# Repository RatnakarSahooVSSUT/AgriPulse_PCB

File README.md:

<div align="center">

# AgriPulse PCB

**Custom Embedded Hardware Design using KiCad**

A custom two-layer PCB designed for the AgriPulse Smart Agriculture Monitoring System, integrating ESP32-based control, agricultural sensor interfaces, RS485 communication and power management.

<br><br>

<br><br>

</div>

---

## Project Overview

AgriPulse is a Smart Agriculture Monitoring System developed to integrate multiple agricultural and environmental sensors into a centralized IoT-based monitoring platform.

This repository contains the custom hardware design developed for the AgriPulse system. The PCB is built around the ESP32 DevKit V1 and provides dedicated interfaces for sensor acquisition, communication, power management and peripheral connectivity.

The design incorporates interfaces for soil moisture monitoring, temperature and humidity sensing, external temperature probes and RS485-based NPK sensor communication.

The objective is to provide a modular and centralized hardware platform for agricultural data acquisition and IoT integration.

---

## PCB Design Gallery

<div align="center">

### 3D PCB Visualization

<br>

### PCB Layout

<br>

### Circuit Schematic

</div>

---

## Hardware Specifications

| Parameter | Specification |
|:---|:---|
| Main Controller | ESP32 DevKit V1 |
| RS485 Transceiver | MAX3485ECSA_T |
| Voltage Regulator | TLV75533PDBV |
| Input Supply | 12V DC |
| Regulated Supply | 3.3V |
| Communication | UART / RS485 |
| Sensor Interfaces | Soil Moisture, DHT22, Temperature Probe |
| PCB Architecture | 2-Layer |
| PCB Design Software | KiCad |
| Component Technology | SMD and Through-Hole |

---

## Power Management

The PCB incorporates a dedicated power input and regulation stage.

- 12V DC barrel jack input.
- Polyfuse-based input protection.
- TVS diode-based transient protection.
- PMOS-based power protection.
- TLV75533PDBV 3.3V voltage regulation.
- Input and output decoupling capacitors.
- Dedicated power and ground distribution.

---

## Sensor & Communication Interfaces

### Sensor Interfacing

- Soil moisture sensor interface.
- DHT22 temperature and humidity interface.
- External temperature probe interface.
- Additional GPIO-based peripheral connections.

### RS485 Communication

The board integrates a MAX3485ECSA_T transceiver for differential communication with external agricultural sensors, including the NPK sensor.

- RS485 A/B differential interface.
- UART communication with ESP32.
- Driver and receiver enable control.
- Dedicated external communication connector.

### User Interface

- Start/Stop push-button interface.
- Screen control button.
- Wi-Fi status indication.
- Alert status indication.
- Start/Stop status indication.

---

## Design Highlights

- ESP32 DevKit V1 integration.
- MAX3485-based RS485 communication.
- Dedicated NPK sensor connectivity.
- Multiple agricultural sensor interfaces.
- 12V DC power input.
- Integrated power protection and 3.3V regulation.
- Dedicated peripheral connectors.
- User control and status indication interfaces.
- Two-layer PCB architecture.
- Custom KiCad symbols, footprints and 3D models.
- Copper routing and GND plane design.
- Dedicated PCB mounting holes.

---

## Major Components

| Component | Function |
|:---|:---|
| ESP32 DevKit V1 | Main controller |
| MAX3485ECSA_T | RS485 transceiver |
| TLV75533PDBV | 3.3V voltage regulator |
| PMOS | Power protection |
| Polyfuse | Input current protection |
| TVS Diode | Transient voltage protection |
| Zener Diode | Voltage protection |
| LEDs | Status indication |
| Capacitors | Filtering and decoupling |
| Resistors | Biasing and current limiting |

---

## PCB Design Tools

<div align="center">

</div>

- **KiCad:** Schematic capture and PCB layout.
- **ESP32:** Embedded controller platform.
- **MAX3485:** RS485 differential communication.
- **Custom Libraries:** Component symbols, footprints and 3D models.

---

## Repository Contents

| File / Folder | Description |
|:---|:---|
| `AgriPulse_pcb.kicad_pro` | Main KiCad project file |
| `AgriPulse_pcb.kicad_pcb` | PCB layout document |
| `AgriPulse_pcb.kicad_sch` | Circuit schematic |
| `Libraries/agripulse.pretty/` | Custom PCB footprints |
| `Libraries/DEVKIT_V1_ESP32-WROOM-32/` | ESP32 symbol, footprint and 3D model |
| `Libraries/MAX3485ECSA_T/` | MAX3485 symbol, footprint and 3D model |
| `images/` | PCB renders, layout and schematic images |
| `.gitignore` | Git version control exclusions |

---

## Getting Started

Clone the repository:

```bash
git clone https://github.com/RatnakarSahooVSSUT/AgriPulse_PCB.git
```

Open `AgriPulse_pcb.kicad_pro` using KiCad.

Configure the custom symbol, footprint and 3D model libraries if required.

The repository includes the schematic, PCB layout and custom component libraries used in the design.

---

## Applications

- Smart agriculture monitoring.
- Soil moisture monitoring.
- Environmental parameter acquisition.
- Temperature and humidity monitoring.
- NPK sensor integration.
- RS485-based agricultural sensor communication.
- IoT-based agricultural data acquisition.

---

## Author

<div align="center">

### Ratnakar Sahoo

**Electronics & Telecommunication Engineering**

Veer Surendra Sai University of Technology (VSSUT), Odisha

Interested in Embedded Systems, PCB Design, Hardware Development, FPGA and IoT Technologies.

<br><br>

</div>

---

<div align="center">

**AGRIPULSE | SMART AGRICULTURE | EMBEDDED SYSTEMS**

Designed with KiCad.

</div>

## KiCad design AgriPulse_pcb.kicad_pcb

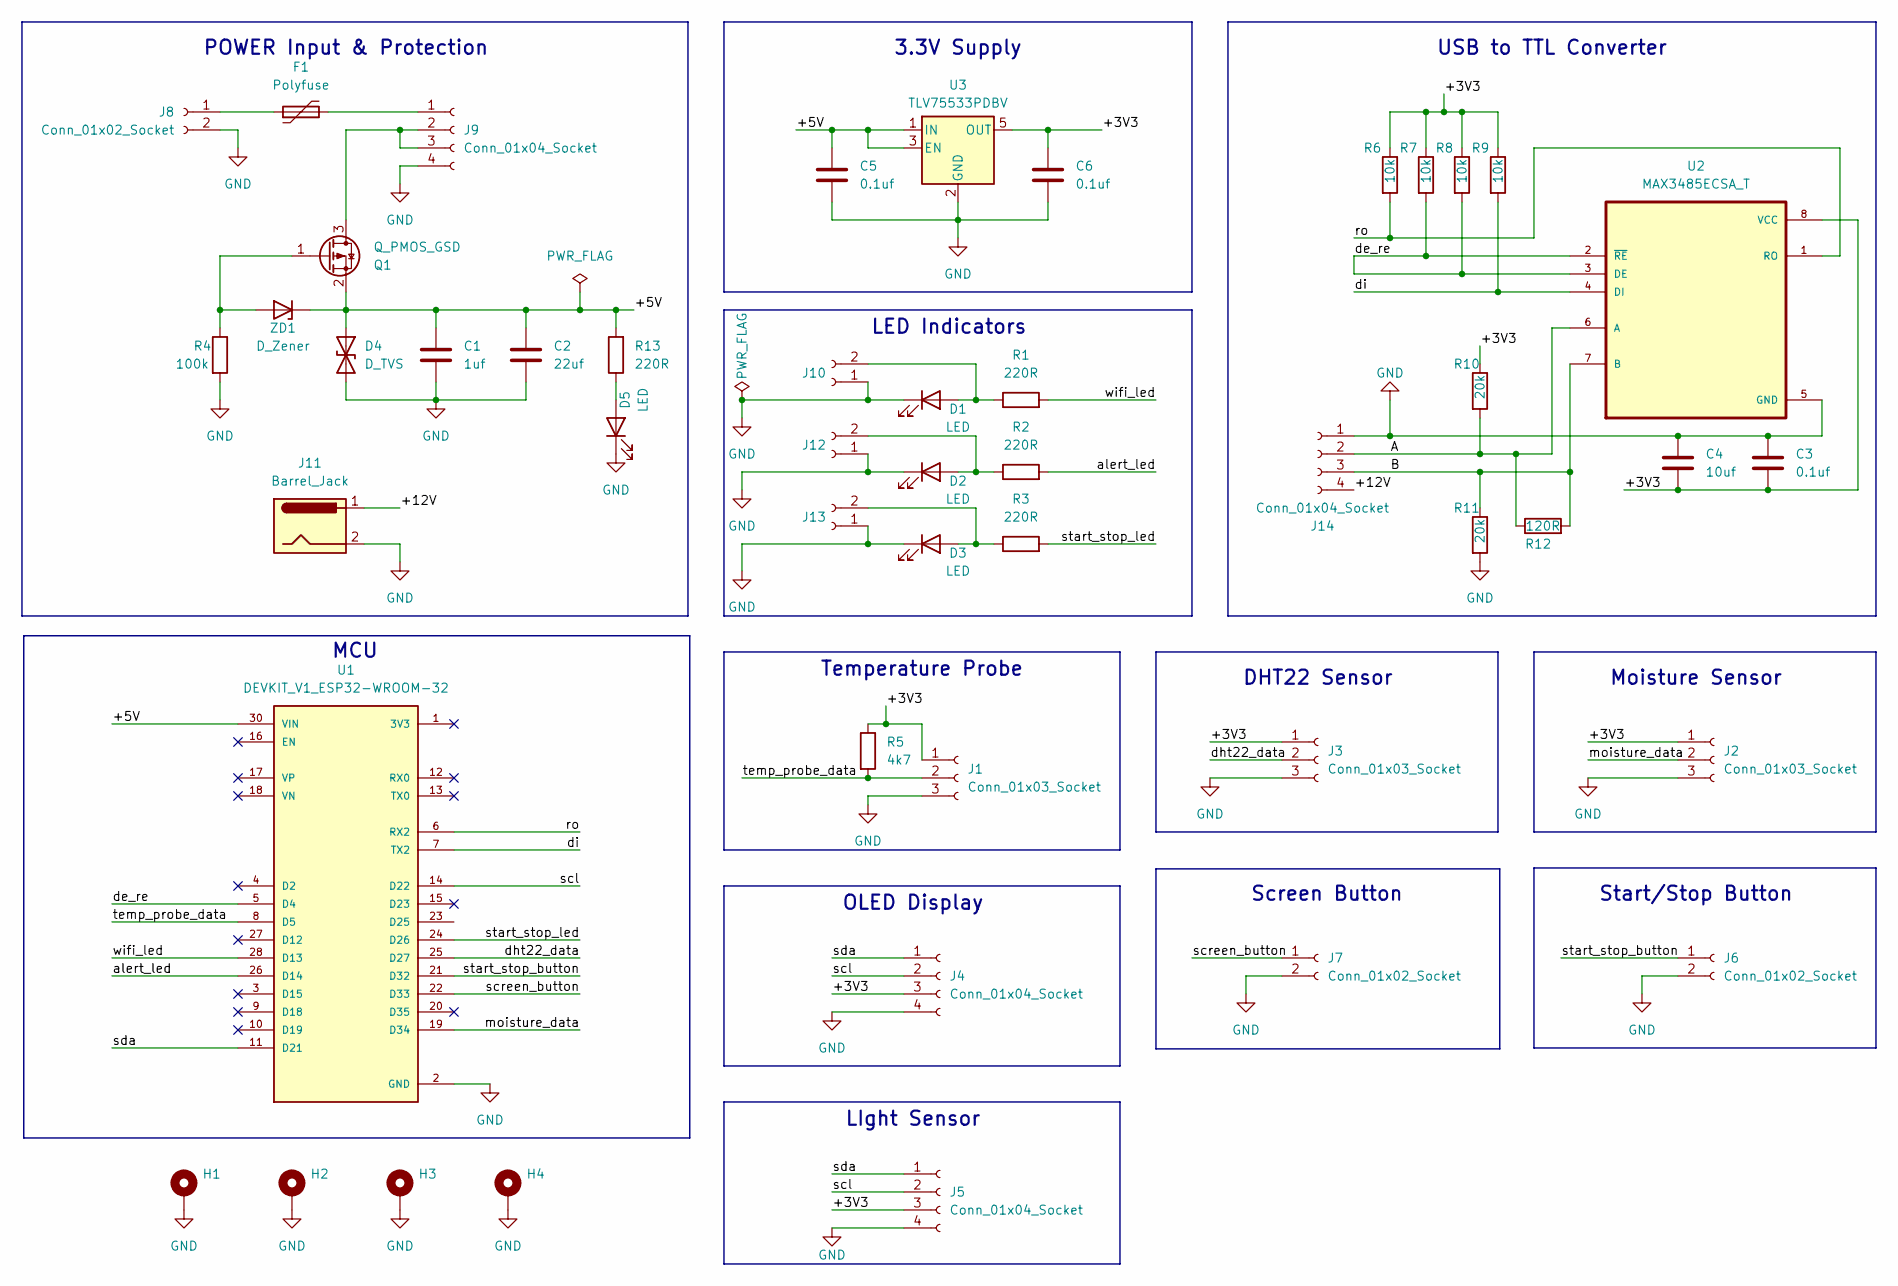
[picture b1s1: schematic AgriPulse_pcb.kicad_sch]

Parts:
C1: 1uf; C_1206_3216Metric_Pad1.33x1.80mm_HandSolder
C2: 22uf; C_1206_3216Metric_Pad1.33x1.80mm_HandSolder
C3, C5, C6: 0.1uf; C_1206_3216Metric_Pad1.33x1.80mm_HandSolder
C4: 10uf; C_1206_3216Metric_Pad1.33x1.80mm_HandSolder
D1, D2, D3, D5: LED; LED_D3.0mm
D4: D_TVS; D_SMB
F1: Polyfuse; Fuse_1812_4532Metric
H1, H2, H3, H4: MountingHole_Pad; MountingHole_2.2mm_M2_Pad_Via
J1, J2, J3: Conn_01x03_Socket; JST_XH_B3B-XH-A_1x03_P2.50mm_Vertical
J4, J5, J9, J14: Conn_01x04_Socket; JST_XH_B4B-XH-A_1x04_P2.50mm_Vertical
J6, J7, J8, J10, J12, J13: Conn_01x02_Socket; JST_XH_B2B-XH-A_1x02_P2.50mm_Vertical
J11: Barrel_Jack; BarrelJack_Horizontal
Q1: Q_PMOS_GSD; SOT-23
R1, R2, R3, R13: 220R; R_1206_3216Metric_Pad1.30x1.75mm_HandSolder
R4: 100k; R_1206_3216Metric_Pad1.30x1.75mm_HandSolder
R5: 4k7; R_1206_3216Metric_Pad1.30x1.75mm_HandSolder
R6, R7, R8, R9: 10k; R_1206_3216Metric_Pad1.30x1.75mm_HandSolder
R10, R11: 20k; R_1206_3216Metric_Pad1.30x1.75mm_HandSolder
R12: 120R; R_1206_3216Metric_Pad1.30x1.75mm_HandSolder
U1: DEVKIT_V1_ESP32-WROOM-32; MODULE_DEVKIT_V1_ESP32-WROOM-32; MPN DEVKIT V1 ESP32-WROOM-32
U2: MAX3485ECSA_T; SOIC127P600X175-8N; MPN MAX3485ECSA+T
U3: TLV75533PDBV; SOT-23-5_HandSoldering
ZD1: D_Zener; D_SOD-323

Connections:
/+3V3: C3.2, C4.2, C6.1, J1.1, J2.1, J3.1, J4.3, J5.3, R5.1, R6.1, R7.1, R8.1, R9.1, R10.1, U2.8 (VCC), U3.5 (OUT)
/+5V: C1.1, C2.1, C5.1, D4.1 (A1), Q1.2 (S), R13.2, U1.30 (VIN), U3.1 (IN), U3.3 (EN), ZD1.1 (K)
/+12V: J11.1, J14.4
/A: J14.2, R10.2, R12.1, U2.6 (A)
/B: J14.3, R11.1, R12.2, U2.7 (B)
/alert_led: R2.2, U1.26 (D14)
/de_re: R7.2, R8.2, U1.5 (D4), U2.2 (~RE), U2.3 (DE)
/dht22_data: J3.2, U1.25 (D27)
/di: R9.2, U1.7 (TX2), U2.4 (DI)
/moisture_data: J2.2, U1.19 (D34)
/ro: R6.2, U1.6 (RX2), U2.1 (RO)
/scl: J4.2, J5.2, U1.14 (D22)
/screen_button: J7.1, U1.22 (D33)
/sda: J4.1, J5.1, U1.11 (D21)
/start_stop_button: J6.1, U1.21 (D32)
/start_stop_led: R3.2, U1.24 (D26)
/temp_probe_data: J1.2, R5.2, U1.8 (D5)
/wifi_led: R1.2, U1.28 (D13)
GND: C1.2, C2.2, C3.1, C4.1, C5.2, C6.2, D1.1 (K), D2.1 (K), D3.1 (K), D4.2 (A2), D5.1 (K), H1.1 (1_1), H2.1 (1_1), H3.1 (1_1), H4.1 (1_1), J1.3, J2.3, J3.3, J4.4, J5.4, J6.2, J7.2, J8.2, J9.4, J10.1, J11.2, J12.1, J13.1, J14.1, R4.2, R11.2, U1.2 (GND), U1.29 (GND), U2.5 (GND), U3.2 (GND)
unnamed: D1.2 (A), J10.2, R1.1
unnamed: D2.2 (A), J12.2, R2.1
unnamed: D3.2 (A), J13.2, R3.1
unnamed: D5.2 (A), R13.1
unnamed: F1.1, J8.1
unnamed: F1.2, J9.1
unnamed: J9.2, J9.3, Q1.3 (D)
unnamed: Q1.1 (G), R4.1, ZD1.2 (A)

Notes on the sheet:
Start/Stop Button
USB to TTL Converter
LIght Sensor
Temperature Probe
Screen Button
POWER Input & Protection
LED Indicators
OLED Display
MCU
3.3V Supply
Moisture Sensor
DHT22 Sensor

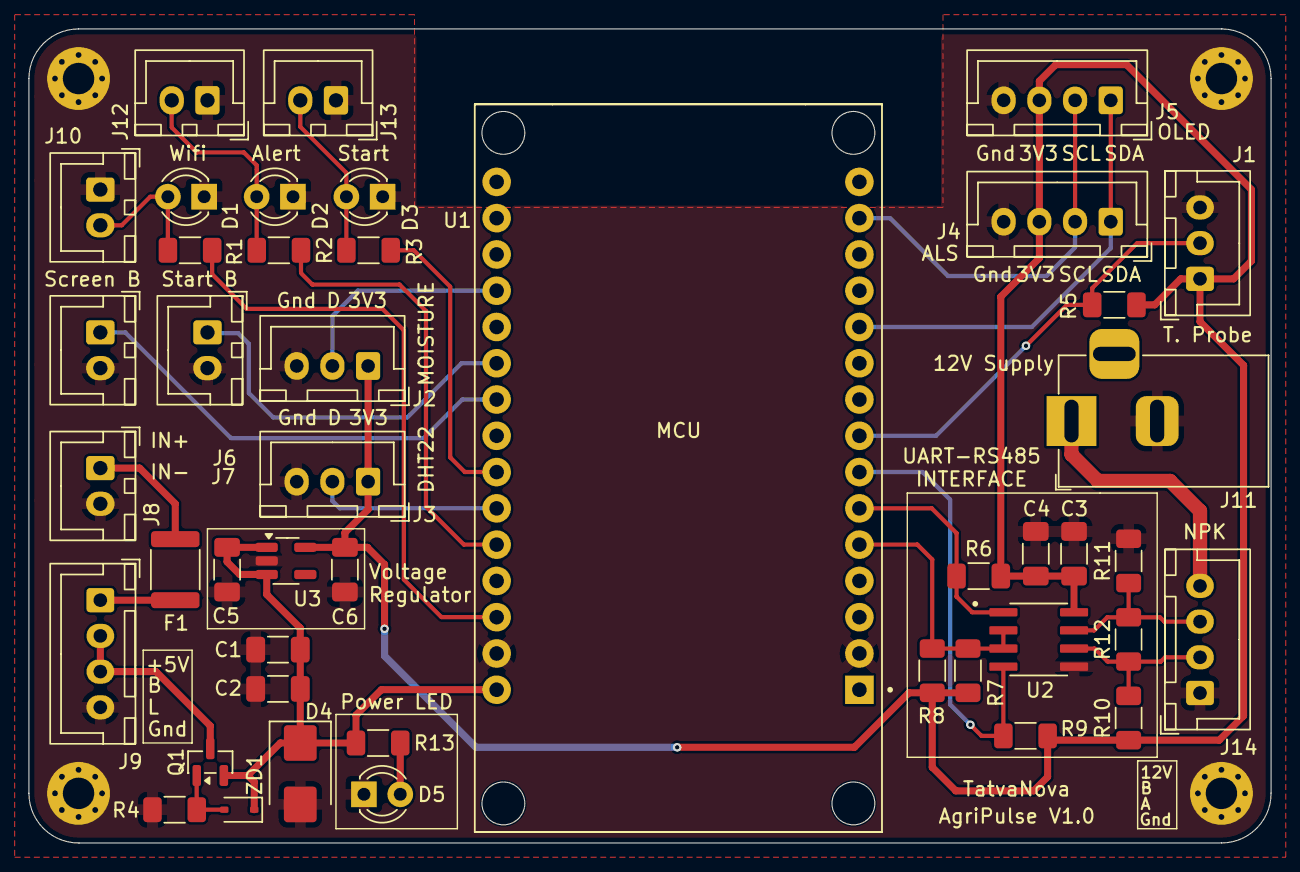
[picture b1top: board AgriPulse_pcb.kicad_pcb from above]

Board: 2 copper layers, 87.0 x 57.0 mm, 48 parts (0 on the bottom side), 27 nets.
